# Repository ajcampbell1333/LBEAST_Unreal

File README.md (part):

# LBEAST SDK for Unreal Engine

**Location-Based Entertainment Activation Standard Toolkit (LBEAST)** - A comprehensive SDK for developing VR/AR Location-Based Entertainment experiences in UE5 with support for AI facial animation, large hydraulic haptics, and embedded systems integration.

<details>
<summary><strong>⚠️Author Disclaimer:</strong></summary>

<blockquote>
This is a brand new plugin as of November 2025. Parts of it are not fully fleshed out. The author built LBE activations for Fortune 10 brands over the past decade. This is the dream toolchain he wishes we had back then, but it probably still contains unforeseen bugs in its current form. V1.0 is considered Alpha, and Alpha is not show-ready. Beta (2.0) will be the first version we attempt to use in professional venues. If you're seeing this message, it's because LBEAST has yet to deploy on a single professional project. Please use this code at your own risk. Also, this plugin provides code that may or may not run on systems your local and state officials may classify as  "amusement rides" or "theme park rides" which may fall under ASTM standards or other local regulations. LBEAST's author disclaims any and all liability for any use of this code, including for safety of guests or patrons, regulatory readiness, etc. Please review the local regulations in your area prior to executing this code in any public venue. You are responsible for compliance in your state.
</blockquote>

</details><br>

---

## 📖 Overview

LBEAST is a comprehensive SDK for developing VR and AR Location-Based Entertainment (LBE) experiences. This repository contains the **Unreal Engine 5.5.4** implementation of the LBEAST SDK.

The LBEAST SDK democratizes LBE development by providing:
- **Experience Genre Templates** - Drag-and-drop complete LBE solutions
- **Low-Level APIs** - Technical modules for custom integration between game engine and various physical systems
- **AI-Driven Facial Animation** for immersive theater live actors (automated w/ NVIDIA ACE)
- **Wireless Trigger Controls** - Embedded buttons in costume/clothing for narrative state machine control through WiFi/Bluetooth
- **Large-Scale Hydraulic Haptics** for lift/motion platforms
- **Embedded Systems Integration** for costume-/prop-/wall-/furniture-mounted interfaces
- **Embedded Sensors** temperature, motion, face, and body tracking sensors to trigger escape room actions
- **Co-located XR Multiplayer LAN Experiences** with Unreal Replication + GAS
- **HMD and Hand Tracking** via OpenXR (Unreal's native XR system)
- **6DOF Tracking** with SteamVR trackers and future extensibility

<details>
<summary><strong>⚠️OpenXR Note:</strong></summary>

<blockquote>
LBEAST uses **OpenXR exclusively** for all HMD and hand tracking access through Unreal Engine's native XR system (`IXRTrackingSystem`, `IHandTracker`). If OpenXR is not desired for your LBE deployment for any reason, but you still want to use an LBEAST experience genre template to get started, there may be some customization necessary in `LBEASTHandGestureRecognizer` and in some of the Experience classes. Anywhere OpenXR is referenced, you may need to create an alternative version of that class with your SDK of choice replacing OpenXR usage.

</blockquote> 

</details>   
<br>

> **🔗 Unity Version:** Also available at [github.com/scifiuiguy/lbeast_unity](https://github.com/scifiuiguy/lbeast_unity)

## 📚 Table of Contents

<details>
<summary><strong>THIS README</strong></summary>

<blockquote>

- [Overview](#overview)
- [Philosophy](#philosophy)
- [Three-Tier Architecture](#three-tier-architecture)
- [Standard Pop-up Layout](#standard-pop-up-layout)
- [Features](#features)
- [Installation](#-installation)
- [Quick Start](#quick-start)
- [Architecture](#architecture)
- [Module Structure](#module-structure)
- [Networking](#networking)
- [Hardware Integration](#hardware-integration)
- [Use Cases](#use-cases)
- [Dedicated Server & Server Manager](#dedicated-server--server-manager)
- [Network Configuration](#network-configuration)
- [Embedded System Philosophy](#embedded-system-philosophy)
- [Embedded System Nuts & Bolts](#-embedded-system-nuts--bolts)
- [Roadmap](#-roadmap)
- [Support](#support)
- [License](#license)
- [Contributing](#contributing)
- [Credits](#credits)

</blockquote>

</details>

<details>
<summary><strong>OTHER READMEs IN THIS PROJECT</strong></summary>

<blockquote>

**Low-Level APIs:**
- [LBEASTAI API README](https://github.com/scifiuiguy/lbeast_unreal/blob/main/Source/LBEASTAI/README.md) - `Source/LBEASTAI/README.md`
- [VRPlayerTransport README](https://github.com/scifiuiguy/lbeast_unreal/blob/main/Source/LBEASTCore/Public/VRPlayerTransport/README.md) - `Source/LBEASTCore/Public/VRPlayerTransport/README.md`
- [Input README](https://github.com/scifiuiguy/lbeast_unreal/blob/main/Source/LBEASTCore/Public/Input/README.md) - `Source/LBEASTCore/Public/Input/README.md`
- [VOIP README](https://github.com/scifiuiguy/lbeast_unreal/blob/main/Source/VOIP/README.md) - `Source/VOIP/README.md`
- [EmbeddedSystems README](https://github.com/scifiuiguy/lbeast_unreal/blob/main/Source/EmbeddedSystems/README.md) - `Source/EmbeddedSystems/README.md`
- [ProLighting README](https://github.com/scifiuiguy/lbeast_unreal/blob/main/Source/ProLighting/README.md) - `Source/ProLighting/README.md`

**Experience Genre Templates:**
- [AIFacemask Experience README](https://github.com/scifiuiguy/lbeast_unreal/blob/main/Source/LBEASTExperiences/Private/AIFacemask/README.md) - `Source/LBEASTExperiences/Private/AIFacemask/README.md`

**Firmware Examples:**
- [FirmwareExamples README](https://github.com/scifiuiguy/lbeast_unreal/blob/main/FirmwareExamples/README.md) - `FirmwareExamples/README.md`
- [GunshipExperience README](https://github.com/scifiuiguy/lbeast_unreal/blob/main/FirmwareExamples/GunshipExperience/README.md) - `FirmwareExamples/GunshipExperience/README.md`
- [FlightSimExperience README](https://github.com/scifiuiguy/lbeast_unreal/blob/main/FirmwareExamples/FlightSimExperience/README.md) - `FirmwareExamples/FlightSimExperience/README.md`
- [SuperheroFlightExperience README](https://github.com/scifiuiguy/lbeast_unreal/blob/main/FirmwareExamples/SuperheroFlightExperience/README.md) - `FirmwareExamples/SuperheroFlightExperience/README.md`
- [EscapeRoom README](https://github.com/scifiuiguy/lbeast_unreal/blob/main/FirmwareExamples/EscapeRoom/README.md) - `FirmwareExamples/EscapeRoom/README.md`
- [Base Examples README](https://github.com/scifiuiguy/lbeast_unreal/blob/main/FirmwareExamples/Base/Examples/README.md) - `FirmwareExamples/Base/Examples/README.md`
- [Base Templates README](https://github.com/scifiuiguy/lbeast_unreal/blob/main/FirmwareExamples/Base/Templates/README.md) - `FirmwareExamples/Base/Templates/README.md`

**Examples & Utilities:**
- [ServerManager README](https://github.com/scifiuiguy/lbeast_unreal/blob/main/Source/Examples/ServerManager/README.md) - `Source/Examples/ServerManager/README.md`

</blockquote>

</details>

---

## 💭 Philosophy

<details>
<summary><strong>Why LBEAST?</strong></summary>

<blockquote>

Home console VR usage is nascent and difficult despite being steadily on the rise:
* 80 million monthly active users in the U.S. in 2025
* up 60% from 2020
* 10% of Americans started using VR regularly so far this decade

If that growth holds, we might reach 100 million regular VR users by end-of-decade, more than 1/4 of the population. It's not smartphone-era growth, but it's steady.

BUT...

Content budgets are skin-and-bone. 

Building for VR requires specialty talent compared to film/TV/gaming, and every dollar spent goes half as far due to...
* deeper fidelity challenges
* bigger QA hurdles
* evil perf op constraints

VR devs need a leg up. The industry has been in a funding desert since the Pandemic. "VR is all hype" rumors put the dev community on a respirator, and we never got off the ropes.

I get where investors are coming from. We're 10 years into modern VR. They need proof of ROI. We need to deliver in the black. We need better tools. We were building cars without factories.

**A good analogy for 21st century VR Distro - Movie Theaters:**
If a Hollywood studio invested millions on a new film in the 80s, they'd be sunk if there were no 35mm projector and no movie theaters hungry to roll the next hit.

**An even better analogy - the JAMMA Arcade Spec:**
In 1985, the arcade industry was in a slump. All the arcade boxes were proprietary. Venues had to buy a new arcade box for every game. Devs had to design a whole arcade box for just THEIR game. Enter the JAMMA Spec. Suddenly venues could leave the same box in place and swap a card, and it's a new game! Same hardware, fresh regular content. Devs could focus on the game knowing reliable hardware was already on-site.

We need that for the VR industry:
* Devs need to be able to focus on dev, not hardware
* Venues need standard hardware so devs can bring them regular new content.

We have an chicken-egg situation. A standard spec for VR LBE is what we need.

Enter LBEAST. Free, open-source, plug-n-play across multiple genres.

</blockquote>

</details>

<details>
<summary><strong>Who is LBEAST for?</strong></summary>

<blockquote>

LBEAST is for VR venues, trade show designers, and professional dev teams designing  permanent, semi-permanent, or pop-up Location-Based Entertainment installations. LBEAST is a professional-grade toolchain designed for teams of programmers and technical artists.

**Target audiences:**
- **Theme park attraction designers/engineers/production staff** - Building immersive attractions with motion platforms, embedded systems, and live actor integration
- **VR Arcade venue designers/engineers/production staff** - Deploying multiplayer VR experiences with synchronized motion and professional audio/lighting
- **Brands at trade shows** interested in wowing audiences with VR
- **3rd-party VR developers** who want to deploy new content rapidly to theme parks and VR Arcades
- **VR educators** who want to expose students to professional toolchains used in commercial LBE production

The SDK provides:
- ✅ **C++ programmers** with robust APIs and extensible architecture
- ✅ **Blueprint artists** with drag-and-drop components and visual scripting
- ✅ **Content teams** with rapid deployment capabilities
- ✅ **Commercial projects** with free-to-use, MIT-licensed code

</blockquote>

</details>

<details>
<summary><strong>Who is LBEAST not for?</strong></summary>

<blockquote>

Developers with little or no experience with C++ may struggle to put LBEAST to its fullest use. It is meant for a scale of production that would be challenging for lone developers. However, it can be a great learning tool for educators to prepare students to work on professional team projects.

**Important notes:**
- LBEAST is **not** a no-code solution. It requires programming knowledge (C++ or Blueprint scripting) to customize experiences beyond the provided templates.
- LBEAST is designed for **team-based production** with multiple developers, technical artists, and production staff.
- LBEAST provides blueprints, but it assumes tech art team members have access to C++ programmers on the team to back them up for customization.

</blockquote>

</details>

---

## 🏗️ Three-Tier Architecture

LBEAST uses a modular three-tier architecture for code organization and server/client deployment.

### Code and Class Structure

<details>
<summary><strong>Tier 1: Low-Level APIs (Technical Modules)</strong></summary>

<blockquote>

Foundation modules providing core functionality:
- `LBEASTCore` - HMD/tracking abstraction, networking
- `LBEASTAI` - Low-level AI API (LLM, ASR, TTS, container management)
- `LargeHaptics` - Platform/gyroscope control
- `EmbeddedSystems` - Microcontroller integration
- `ProAudio` - Professional audio console control via OSC
- `ProLighting` - DMX lighting control (Art-Net, USB DMX)
- `Retail` - Cashless tap card payment interface for VR tap-to-play
- `VOIP` - Low-latency voice communication with 3D HRTF spatialization
- `RF433MHz` - 433MHz RF trigger/receiver API for wireless button/remote control (rolling code support, USB receiver abstraction)

**Use these when:** Building custom experiences from scratch with full control.

</blockquote>

</details>

<details>
<summary><strong>Tier 2: Experience Genre Templates (Pre-Configured Actors)</strong></summary>

<blockquote>

Ready-to-use complete experiences combining multiple APIs:
- `AAIFacemaskExperience` - Live actor-driven multiplayer VR with wireless trigger buttons controlling automated AI facemask performances
- `AMovingPlatformExperience` - A 4-gang hydraulic platform on which a single VR player stands while hooked to a suspended cable harness to prevent falling
- `AGunshipExperience` - 4-player seated platform with 4DOF hydraulic motion driven by a 4-gang actuator platform with a player strapped in at each corner, all fixed to a hydraulic lift that can dangle players a few feet in the air
- `ACarSimExperience` - A racing/driving simulator where 1-4 player seats are bolted on top of a 4-gang hydraulic platform
- `AFlightSimExperience` - A single player flight sim with HOTAS controls in a 2-axis gyroscopic cockpit built with servo motors for pitch and roll.
  - **⚠️ Requires outside-in tracking with cockpit-mounted trackers for Space Reset feature (see FlightSimExperience/README.md)** 
- `AEscapeRoomExperience` - Puzzle-based escape room with embedded door lock/prop latch solenoids, sensors, and pro AV integration for light/sound and live improv actors
- `AGoKartExperience` - Electric go-karts, bumper cars, race boats, or bumper boats augmented by passthrough VR or AR headsets enabling overlaid virtual weapons and pickups that affect the performance of the vehicles
- `ASuperheroFlightExperience` - A dual-hoist-harness-and-truss system that lifts a player into the air and turns them prone to create the feeling of superhero flight as they punch fists out forward, up, or down

**Use these when:** Rapid deployment of standard LBE genres.

</blockquote>

</details>

<details>
<summary><strong>Tier 3: Your Custom Game Logic</strong></summary>

<blockquote>

Build your specific experience (Tier 3) on top of templates (Tier 2) or APIs (Tier 1).

</blockquote>

</details>

<details>
<summary><strong>When to Use What?</strong></summary>

<blockquote>

| Scenario | Use This | Why |
|----------|----------|-----|
| Building a gunship VR arcade game | `AGunshipExperience` | Pre-configured for 4 players, all hardware setup included |
| Building a racing game | `ACarSimExperience` | Simplified driving API, optimized motion profiles |
| Building a space combat game | `AFlightSimExperience` | HOTAS integration ready, continuous rotation supported |
| Custom 3-player standing platform | Low-Level APIs | Need custom configuration not covered by templates |
| Live actor-driven escape room | `AAIFacemaskExperience` | Wireless trigger buttons in costume control narrative state machine, automated AI facemask performances |
| Puzzle-based escape room | `AEscapeRoomExperience` | Narrative state machine, door locks, prop sensors, embedded systems |
| Go-kart racing with VR/AR overlay | `AGoKartExperience` | Passthrough VR/AR support, virtual weapons, item pickups, projectile combat |
| Superhero flight simulation | `ASuperheroFlightExperience` | Dual-winch suspended harness, gesture-based control, free-body flight |
| Unique hardware configuration | Low-Level APIs | Full control over all actuators and systems |

**Rule of thumb:** Start with templates, drop to APIs only when you need customization beyond what templates offer.

</blockquote>

</details>

### LAN Server/Client Configuration

<details>
<summary><strong>Local Command Console</strong></summary>

<blockquote>

```
┌─────────────────────────────────────────────────┐
│  Single PC (Command Console + Server Manager)   │
│  ─────────────────────────────────────────────  │
│  • Command Console UI (UMG Panel)               │
│  • Server Manager (Dedicated Server Backend)    │
│  • All processing on one machine                │
└──────────────────────┬──────────────────────────┘
                       │
                       │ UDP WiFi (LAN)
                       │
        ┌──────────────┴──────────────┐
        │                             │
        ▼                             ▼
   ┌─────────┐                  ┌─────────┐
   │ VR HMD  │                  │ VR HMD  │
   │(Player) │                  │(Live    │
   │   1     │                  │ Actor 1)│
   └─────────┘                  └─────────┘
        │                             │
        │                             │
   ┌────┴────┐                  ┌────┴────┐
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
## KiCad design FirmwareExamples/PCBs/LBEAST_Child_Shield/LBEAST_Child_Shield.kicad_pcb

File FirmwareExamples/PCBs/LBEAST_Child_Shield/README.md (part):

# LBEAST Child Shield

**Also known as:** LBCS

## Overview

The Child Shield is a simplified derivative of the Universal Shield (LBUS). It keeps the same ESP32-S3 parent ECU pin map and Ethernet PHY but reduces the aux bus to **one** RJ45 port and drops CAN entirely. The goal is to provide a tiny, inexpensive parent/child hybrid board for installations that only need a single downstream device or a dedicated “mini LBUS” inside a prop or remote enclosure.

**Current design goals:**
- 1× RJ45 (Ethernet only). No CAN, no extra ADC/PWM breakouts.
- Powered either from the parent LBUS via the PoE/DIP/diode rail **or** from a local USB‑C Li‑ion pack (5 V input only).
- No onboard buck converter, reverse-polarity MOSFET, or fan header—the board expects regulated 5 V and relies on passive cooling.
- Keep the ESP32-S3 personality-adapter footprint for firmware parity with LBUS.
- Target the smallest possible PCB outline for costume props, handheld gadgets, and wireless sensor clusters.

> Until this document is fleshed out, refer to the [Universal Shield README](../LBEAST_Universal_Shield/README.md) for fully documented schematics, BOM, and power notes. The Child Shield uses that design as its baseline.

---

## Documentation Template (to be completed)

The sections below intentionally keep the same structure as the Universal Shield README. Each section contains a short note describing what still needs to be written for the Child Shield variant.

<details>
<summary><strong>Electronic Control Unit (ECU)</strong></summary>

<div style="margin-left: 20px;">
Provide a summarized ECU primer tailored to the Child Shield. Emphasize that this board is meant for ultra-lightweight, Ethernet-only nodes (wearables, handheld props, remote sensors) that either sip power from LBUS or carry their own USB‑C battery.
</div>

</details>

<details>
<summary><strong>Child Shield Role in the LBUS Ecosystem</strong></summary>

<div style="margin-left: 20px;">
Explain how the Child Shield can operate as:
- A “micro parent” when only one Ethernet child device is required.
- A pre-wired breakout that ships with finished props or costume pieces (power via USB‑C).
- A remote Ethernet-only repeater that backhauls data to a full LBUS when PoE is toggled on.
Document the rules for when to toggle PoE off (battery-powered mode) vs on (LBUS-powered mode), and reiterate that no CAN bus is present on this variant.
</div>

</details>

<details>
<summary><strong>Motivation / Modularity Advantage</strong></summary>

<div style="margin-left: 20px;">
Describe the cost/space savings of a single-port shield vs. an 8-port backplane. Document the target BOM (<$15 at scale) and the intended use cases (wearables, props, distributed IoT nodes).
</div>

</details>

<details>
<summary><strong>Key Features (Child Shield)</strong></summary>

<div style="margin-left: 20px;">
- 1× RJ45 aux port (Ethernet only; same pin map as AUX1 on LBUS)
- ESP32-S3 socket (same as Universal Shield) for firmware compatibility
- Power flexibility: accepts 5 V from LBUS PoE rail or from local USB‑C input
- No CAN transceiver, no LM2576 buck converter, no fan header
- Reduced board outline sized for small enclosures (exact dimensions TBD)
</div>

</details>

<details>
<summary><strong>High-Level Block Diagram</strong></summary>

<div style="margin-left: 20px;">
Add a simplified ASCII diagram once schematic capture begins. Use the Universal Shield diagram as a starting point, but replace the 8-port block with a single “Aux Port J1” call-out.
</div>

</details>

<details>
<summary><strong>Project Files</strong></summary>

<div style="margin-left: 20px;">
Planned filenames (to be created when schematic/PCB are captured):
- `LBEAST_Child_Shield.kicad_pro`
- `LBEAST_Child_Shield.kicad_sch`
- `LBEAST_Child_Shield.kicad_pcb`
- `LBEAST_Child_Shield.kicad_prl`
Note: Until those exist, the folder contains a working copy of the Universal Shield project as a springboard.
</div>

</details>

<details>
<summary><strong>Power Architecture</strong></summary>

<div style="margin-left: 20px;">
Document the simplified power path:
- 5 V PoE from LBUS → DIP switch → diode → RJ45 pin 4
- Optional USB‑C 5 V input (with reverse-current blocking so it doesn’t backfeed LBUS)
- ESP32-S3 VIN receives 5 V directly (no onboard buck). Note USB‑C current limit assumptions.
Clarify fuse strategy (likely deferred to parent LBUS) and diode usage.
</div>

</details>

<details>
<summary><strong>Component Set / BOM</strong></summary>

<div style="margin-left: 20px;">
Create a slimmed-down BOM once the schematic is finalized. Expected parts:
- ESP32-S3 headers + UART debug header
- LAN8720A PHY + 25 MHz crystal + magnetics
- Single RJ45 (MTJ-883X1 or similar)
- USB‑C connector (5 V only, no PD)
- DIP switch + Schottky diode for PoE gating
- Bypass caps, status LEDs, optional ESD protection
</div>

</details>

<details>
<summary><strong>Aux Port Pinout (Single-Port)</strong></summary>

<div style="margin-left: 20px;">
Reuse the T568B table from the Universal Shield but annotate that only J1 exists. Clarify how ADC/PWM mapping changes (likely reusing AUX1 nets).
</div>

</details>

<details>
<summary><strong>Enclosure / Mechanical Notes</strong></summary>

<div style="margin-left: 20px;">
- Planned enclosure: **Polycase TerraForm TF-1741TX** (ABS, tool-less lid) – [Product page](https://www.polycase.com/tf-1741tx). Fits a single RJ45, USB-C, and low-profile ESP32 module. Document mounting-hole pattern once the PCB outline is finalized.
- Add measurements for the smaller board, recommended potting volumes, and any mounting-hole changes once the layout exists. Capture whether standoffs align with the TF-1741TX bosses or require adhesive-backed posts.
</div>

</details>

<details>
<summary><strong>Future Work</strong></summary>

<div style="margin-left: 20px;">
- Finalize schematic/layout
- Generate dedicated 3D models and assembly drawings
- Produce a minimal BOM + fabrication notes
- Write firmware notes for "single-port parent" mode
- **TP4056 Battery Integration** - Integrate TP4056 USB-C lithium battery charging module directly onto the Child Shield PCB with exposed battery connection pads (B+/B-). Enables portable, battery-powered operation for wearable props, handheld gadgets, and remote sensor clusters. Includes power path management (USB-C charging + battery power), boost converter for 5V output (ESP32 dev board compatibility), and battery protection circuitry. See v2.0 roadmap for implementation details.
</div>

</details>

<details>
<summary><strong>High-Level Component Diagram</strong></summary>

<div style="margin-left: 20px;">

```
          ┌────────────────────────────────────────┐
          |                                        │
    ┌─────▲───────┐    ┌───────┐ +5V               │
    │ Barrel Jack │───→│LM2576 │────┐       ┌──────▼───────┐
    │  12V/24V    │    │ Buck  │    │       │ 12/24V Fan   │
    └─────────────┘    └───────┘    │       └───────┬──────┘
                           │+5V     │               ▼
                           │        │  ┌────────────────────────┐
                           │        └─→│         ESP32-S3       │
                           │           │      (Motherboard)     │
                           │           └──▲──────────────▲──────┘
                           │              │              │
                           │         ┌────▼────┐    ┌────▼────┐
                           │         │LAN8720A │    │ADM3057E │
                           │         │Ethernet │    │ CAN-FD  │
                           │         └────▲────┘    └────▲────┘
                           │              │              │
                           │              │         ┌────▼─────┐
                           │              │         │CAN 3-pin │
                           │              │         └──────────┘         
                    ┌──────▼──────────────▼──────────────────┐   
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
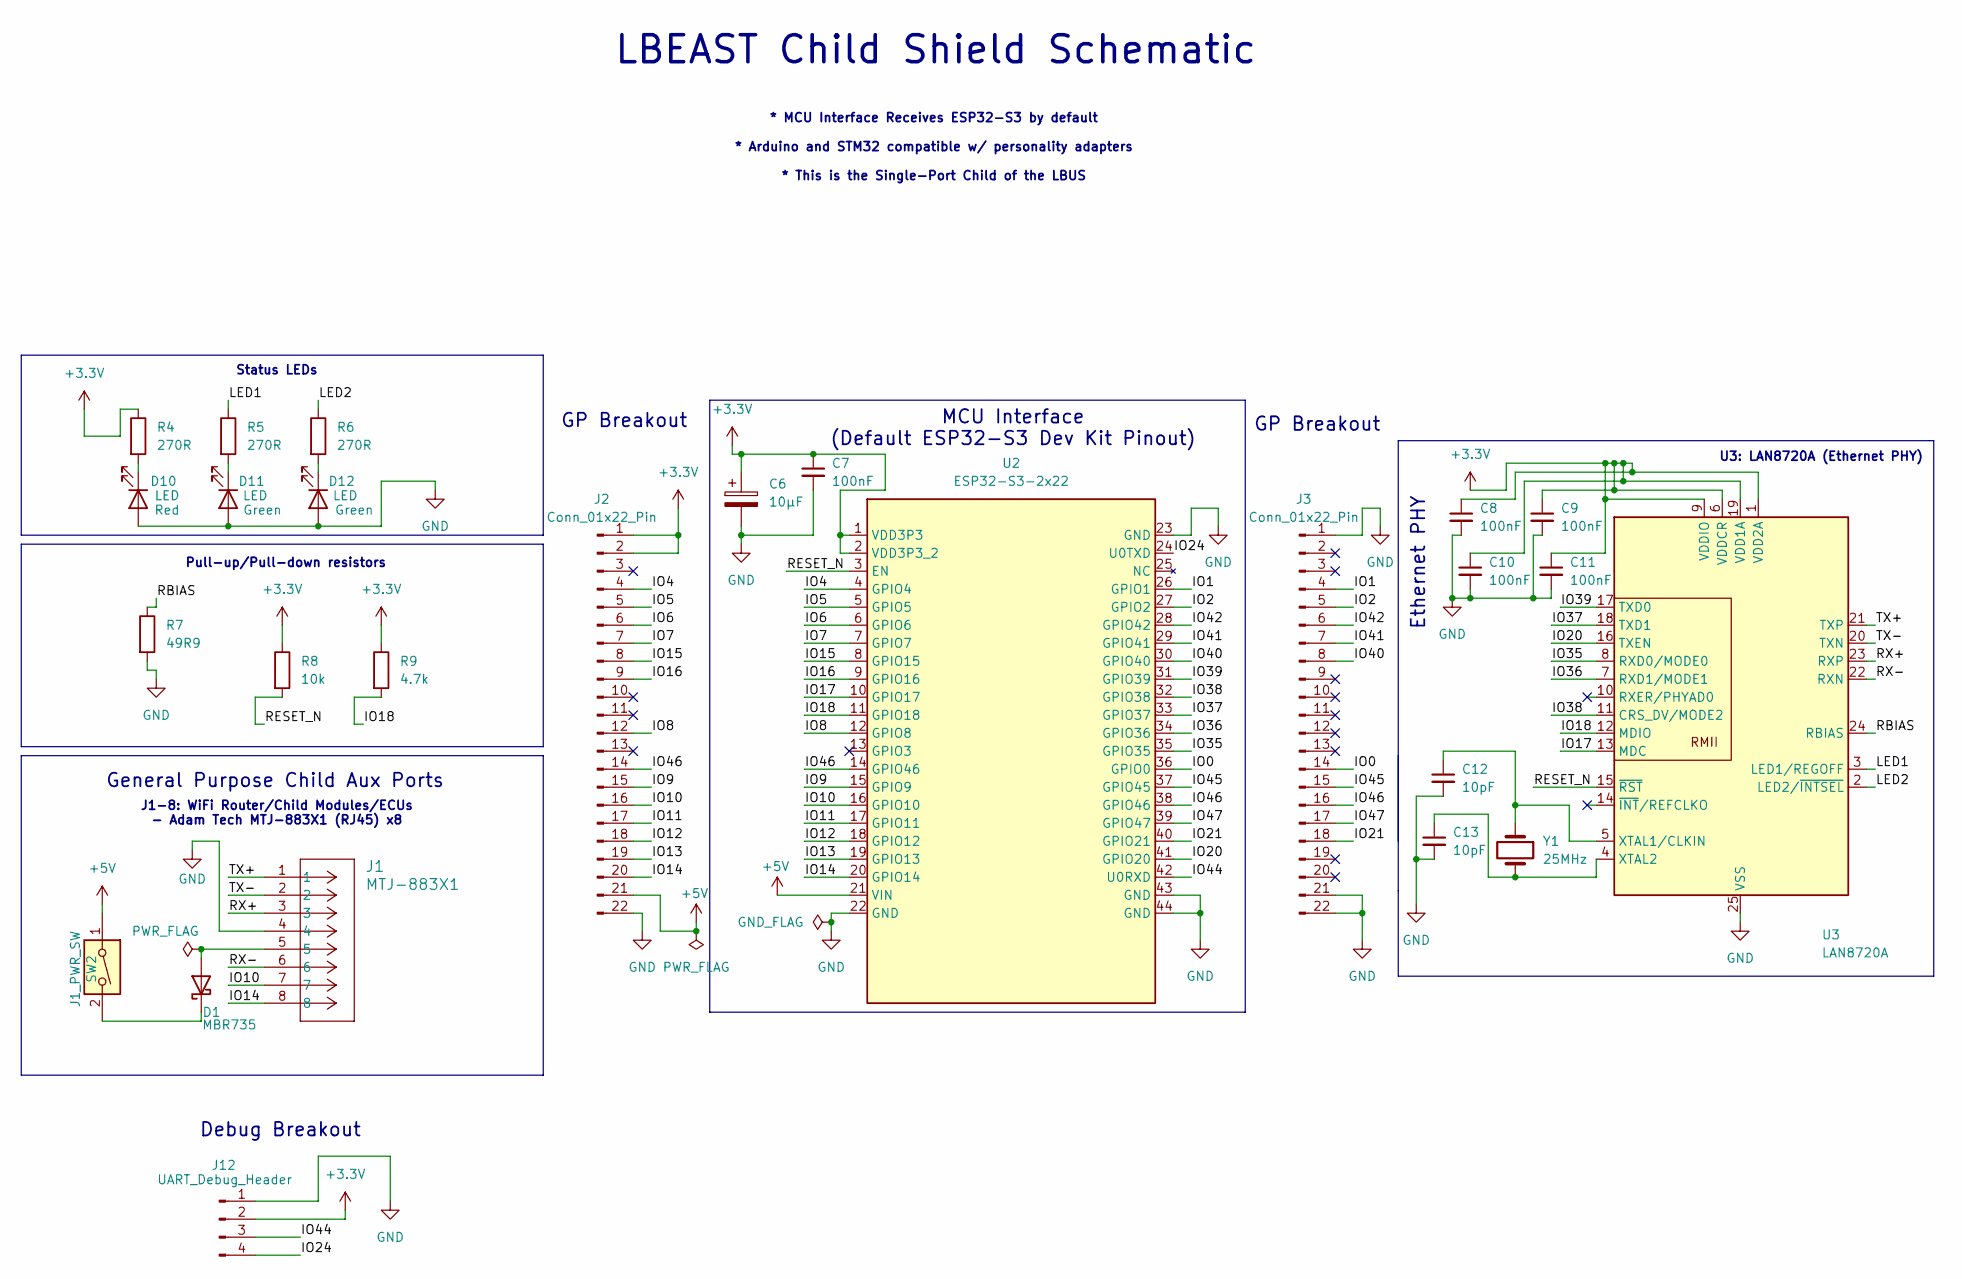
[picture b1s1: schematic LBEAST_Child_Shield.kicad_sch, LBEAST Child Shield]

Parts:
C6: 10µF; CP_EIA-3216-18_Kemet-A
C7, C8, C9, C10, C11: 100nF; C_0805_2012Metric
C12, C13: 10pF; C_0805_2012Metric
D1: MBR735; TO-220-2_Vertical
D10, D11, D12: LED; LED_0805_2012Metric
J1: MTJ-883X1; CONN_MTJ-883X1_ADM
J2, J3: Conn_01x22_Pin; PinHeader_1x22_P2.54mm_Vertical
J12: UART_Debug_Header; PinHeader_1x04_P2.54mm_Vertical
R4, R5, R6: 270R; R_0805_2012Metric
R7: 49R9; R_0805_2012Metric
R8: 10k; R_0805_2012Metric
R9: 4.7k; R_0805_2012Metric
SW2: J1_PWR_SW; SW_DIP_SPSTx01_Slide_6.7x4.1mm_W6.73mm_P2.54mm_LowProfile_J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
U2: ESP32-S3-2x22; ESP32-S3_2x22_Header_v3
U3: LAN8720A; VQFN-24-1EP_4x4mm_P0.5mm_EP2.5x2.5mm_ThermalVias
Y1: 25MHz; Crystal_SMD_3225-4Pin_3.2x2.5mm

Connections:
+3.3V: C6.1, C7.1, C8.1, C9.1, C10.1, C11.1, J2.1, J2.2, J12.2, R4.1, R8.1, R9.1, U2.1 (VDD3P3), U2.2 (VDD3P3_2), U3.1 (VDD2A), U3.6 (VDDCR), U3.9 (VDDIO), U3.19 (VDD1A)
+5V: J2.21, SW2.1, U2.21 (VIN)
/IO0: J3.14, U2.36 (GPIO0)
/IO1: J3.4, U2.26 (GPIO1)
/IO2: J3.5, U2.27 (GPIO2)
/IO4: J2.4, U2.4 (GPIO4)
/IO5: J2.5, U2.5 (GPIO5)
/IO6: J2.6, U2.6 (GPIO6)
/IO7: J2.7, U2.7 (GPIO7)
/IO8: J2.12, U2.12 (GPIO8)
/IO9: J2.15, U2.15 (GPIO9)
/IO10: J1.7, J2.16, U2.16 (GPIO10)
/IO11: J2.17, U2.17 (GPIO11)
/IO12: J2.18, U2.18 (GPIO12)
/IO13: J2.19, U2.19 (GPIO13)
/IO14: J1.8, J2.20, U2.20 (GPIO14)
/IO15: J2.8, U2.8 (GPIO15)
/IO16: J2.9, U2.9 (GPIO16)
/IO17: U2.10 (GPIO17), U3.13 (MDC)
/IO18: R9.2, U2.11 (GPIO18), U3.12 (MDIO)
/IO20: U2.41 (GPIO20), U3.16 (TXEN)
/IO21: J3.18, U2.40 (GPIO21)
/IO24: J12.4, U2.24 (U0TXD)
/IO35: U2.35 (GPIO35), U3.8 (RXD0/MODE0)
/IO36: U2.34 (GPIO36), U3.7 (RXD1/MODE1)
/IO37: U2.33 (GPIO37), U3.18 (TXD1)
/IO38: U2.32 (GPIO38), U3.11 (CRS_DV/MODE2)
/IO39: U2.31 (GPIO39), U3.17 (TXD0)
/IO40: J3.8, U2.30 (GPIO40)
/IO41: J3.7, U2.29 (GPIO41)
/IO42: J3.6, U2.28 (GPIO42)
/IO44: J12.3, U2.42 (U0RXD)
/IO45: J3.15, U2.37 (GPIO45)
/IO46: J2.14, J3.16, U2.14 (GPIO46), U2.38 (GPIO46)
/IO47: J3.17, U2.39 (GPIO47)
/LED1: R5.1, U3.3 (LED1/REGOFF)
/LED2: R6.1, U3.2 (LED2/~INTSEL)
/RBIAS: R7.1, U3.24 (RBIAS)
/RESET_N: R8.2, U2.3 (EN), U3.15 (~RST)
/RX+: J1.3, U3.23 (RXP)
/RX-: J1.6, U3.22 (RXN)
/TX+: J1.1, U3.21 (TXP)
/TX-: J1.2, U3.20 (TXN)
GND: C6.2, C7.2, C8.2, C9.2, C10.2, C11.2, C12.2, C13.2, D10.2 (A), D11.2 (A), D12.2 (A), J1.4, J2.22, J3.1, J3.21, J3.22, J12.1, R7.2, U2.22 (GND), U2.23 (GND), U2.43 (GND), U2.44 (GND), U3.25 (VSS), Y1.3
unnamed: D1.2 (A), J1.5
unnamed: D1.1 (K), SW2.2
unnamed: D10.1 (K), R4.2
unnamed: D11.1 (K), R5.2
unnamed: D12.1 (K), R6.2
unnamed: C12.1, U3.5 (XTAL1/CLKIN), Y1.1
unnamed: C13.1, U3.4 (XTAL2), Y1.2

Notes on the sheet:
GP Breakout
J1-8: WiFi Router/Child Modules/ECUs - Adam Tech MTJ-883X1 (RJ45) x8
General Purpose Child Aux Ports
Debug Breakout
Ethernet PHY
Pull-up/Pull-down resistors
U3: LAN8720A (Ethernet PHY)
* MCU Interface Receives ESP32-S3 by default * Arduino and STM32 compatible w/ personality adapters * This is the Single-Port Child of the LBUS
LBEAST Child Shield Schematic
Status LEDs
MCU Interface (Default ESP32-S3 Dev Kit Pinout)

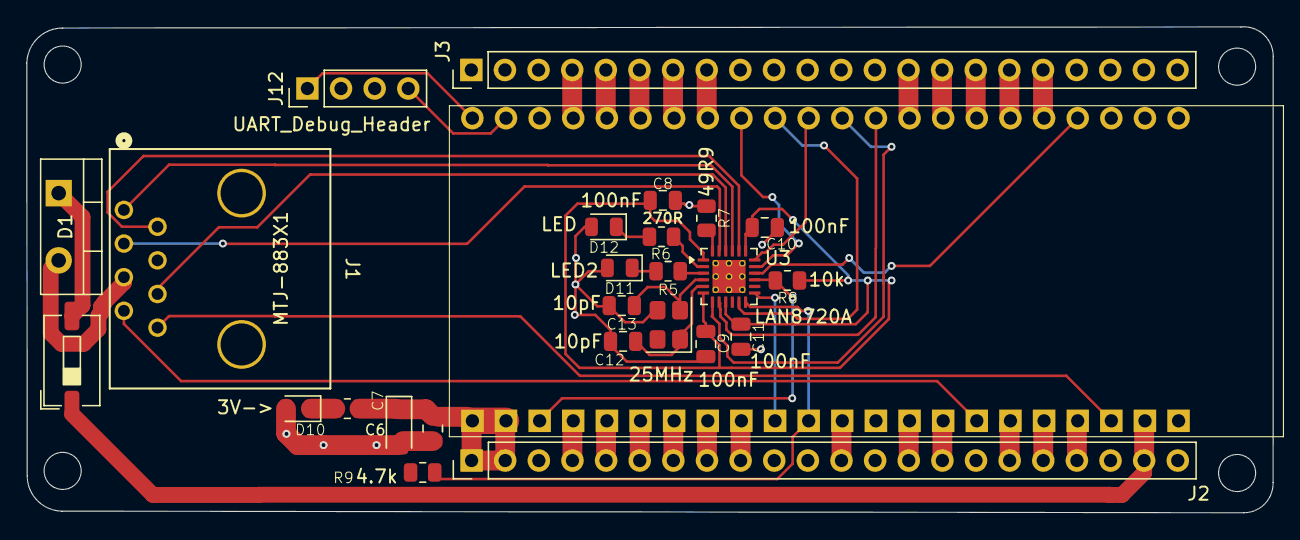
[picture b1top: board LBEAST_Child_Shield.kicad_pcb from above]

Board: 2 copper layers, 94.1 x 36.7 mm, 26 parts (0 on the bottom side), 51 nets.

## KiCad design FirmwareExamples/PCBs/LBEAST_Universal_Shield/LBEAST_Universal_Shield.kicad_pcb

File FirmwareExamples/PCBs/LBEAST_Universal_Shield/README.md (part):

# LBEAST Universal Shield

**Also known as:** LBUS, Uni-Shield

## Overview

**Plug-n-Play Embedded Systems - an Absolute Necessity for Next-Level LBE:**

The LBEAST Universal Shield ("LBUS" or "Uni-Shield") is a multi-platform ECU that provides unified connectivity and control for all LBEAST firmware applications. But what is it for? What does it do? ECU? What the heck is even that?

<details>
<summary><strong>Electronic Control Unit (ECU)</strong></summary>

<div style="margin-left: 20px;">

It's sort of like the little computer hidden behind the dashboard in your car. It's not a supercomputer... quite the opposite. It costs a few dollars to buy a few dev boards on Amazon and deploy them as ECUs by flashing programs onto them. If you've done IoT with Arduino, ESP32, or STM32... congrats! You're an ECU programmer!

ECUs are nowhere near as powerful or expensive as a smartphone, but they can be MUCH smaller and lighter, so they're great for speciatly tasks hidden in tight spaces. Custom-built processors with dedicated task lists... hardware AND firmware are built to do that task list and nothing more. You don't run a program from a list of programs. The whole ECU's operating system IS the program. It's a one-program device. That's why we say "firmware." To update or replace the latest build, you flash A.K.A. replace all the code running on the device.

</div>

</details>

<details>
<summary><strong>LBUS is an ECU Network</strong></summary>

<div style="margin-left: 20px;">

LBUS is the ECU you should start with for LBEAST-ready installations, and it can netowrk with copies of itself or any other custom ECU that communicates over ethernet, bluetooth, 433MHz RF, and/oror Wifi. It's powered by your choice of ESP32, Arduino, or STM32. LBUS serves as Union Station for all the data in any system you build from scratch. It enables you to deploy hydraulics, haptics, big servo motors that can spin customers upside down, etc. It let's you hide Child ECUs inside the chassis of a ride, in the clothing of immersive actors, in props, and/or in the decorated walls of an AR experience.

</div>

</details>

<details>
<summary><strong>Doesn't the LBE Industry already do things like this?</strong></summary>

<div style="margin-left: 20px;">

Most VR and AR experiences are driven by local multiplayer servers built via game engines so that co-located players can see a shared experience while an employee monitors the state of the game loop. Occasionally, these LBE events have advanced integration with a variety of other systems, including lights, pro audio, communication with smartphones and tablets for extra control.

However, it is rare to see a VR experience that includes theme-park attraction technology like large hydraulic actuators or embedded ECUs in costumes worn by immersive actors, in props, and in scenery. This is because the full palette of immersive technologies is complex and expensive. VR budgets in the 2020s generally prohibit us from "next-level"-ing VR experiences in most cases. It's not that we can't integrate the tech. It has just been TOO EXPENSIVE.

</div>

</details>

<details>
<summary><strong>The LBUS Fixes That!</strong></summary>

<div style="margin-left: 20px;">

LBUS is open-source. It's near free! And it's already fully built and running, ready for you to take and use and skin it with new assets and stand up a new LBE event in a fraction of the time!

LBUS fully integrated with both major game engines (Unity/Unreal) in a ready-to-play local multiplayer server project that has a bunch of LBE templates ready-to-play. A single out-of-the-box LBUS has a bill-of-materials of less than $200 to build 5 copies. LBEAST is not a company. The PCB files are in the git repo, ready for you to send to any PCB manufacturer to order boards at a tiny fraction of the cost of using PLCs. A single LBUS unit supports 8 simultaneous child ECUs via Ethernet while providing galvanically isolated CAN-FD connectivity for high-current device control.

</div>

</details>

<details>
<summary><strong>Just like JAMMA Resurrected the Arcade Industry in 1985</strong></summary>

<div style="margin-left: 20px;">

The whole industry was proprietary and in a big recession. Developers and venues needed a leg up. Arcade retailers were struggling with the cost of buying anew arcade box every time a new game came out.

Suddenly, the JAMMA spec let them pop a new game card into the same box they already had. Games started launching 10X as fast as before. New content every day! Developers didn't have to worry about box manufacture anymore. They could just focus on the game.

VR is VERY proprietary today. What if you want to build a hydraulic sim and make it feel like a theme park ride? Where do you even begin? You have to hire mechanical engineers and software engineers, and they'll build a complex sytem that works ONLY at your venue. Good luck getting 10 VR development teams to build something for that.

The industry needs standard specs. If you already built a hydraulic rig to a known spec, and EVERY VR dev team knows that spec already, they can ALL starting building experiences for it. It's a chicken/egg challenge, and neither can happen first until we have a spec. That's why LBUS is critical for VR2.0.

</div>

</details>

<details>
<summary><strong>Modularity Advantage</strong></summary>

<div style="margin-left: 20px;">

Unlike traditional PLCs (Programmable Logic Controllers) that require proprietary hardware and software ecosystems, the Universal Shield embraces modularity through open-source microcontrollers. This approach offers several key advantages: **cost efficiency** (microcontrollers are significantly less expensive than PLCs), **flexibility** (choose the MCU platform that best fits your application), **rapid development** (standard development tools and languages), **scalability** (easily expand with additional child ECUs), and **future-proofing** (upgrade individual components without replacing entire systems). The Universal Shield's personality adapter system allows the same hardware to support multiple MCU platforms, while the 8-port Ethernet architecture enables distributed processing across a network of child ECUs, creating a flexible, scalable control architecture that adapts to project requirements.

</div>

</details>

<details>
<summary><strong>Key Features</strong></summary>

<div style="margin-left: 20px;">

- Multi-platform support: ESP32-S3 (native) &  STM32/Arduino (via personality adapters)
- 8× CAT5 aux ports for child ECUs (Raspberry Pi, Jetson, ESP32, STM32, Arduino)
- Isolated CAN-FD transceiver for high-current device control
- 100 Mbps Ethernet connectivity
- 12V/24V input with 5V power distribution (≥5A total capacity)
- Designed for potting and long-term installations

</div>

</details>

<details>
<summary><strong>High-Level Component Diagram</strong></summary>

<div style="margin-left: 20px;">

```
          ┌────────────────────────────────────────┐
          |                                        │
    ┌─────▲───────┐    ┌───────┐ +5V               │
    │ Barrel Jack │───→│LM2576 │────┐       ┌──────▼───────┐
    │  12V/24V    │    │ Buck  │    │       │ 12/24V Fan   │
    └─────────────┘    └───────┘    │       └───────┬──────┘
                           │+5V     │               ▼
                           │        │  ┌────────────────────────┐
                           │        └─→│         ESP32-S3       │
                           │           │      (Motherboard)     │
                           │           └──▲──────────────▲──────┘
                           │              │              │
                           │         ┌────▼────┐    ┌────▼────┐
                           │         │LAN8720A │    │ADM3057E │
                           │         │Ethernet │    │ CAN-FD  │
                           │         └────▲────┘    └────▲────┘
                           │              │              │
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
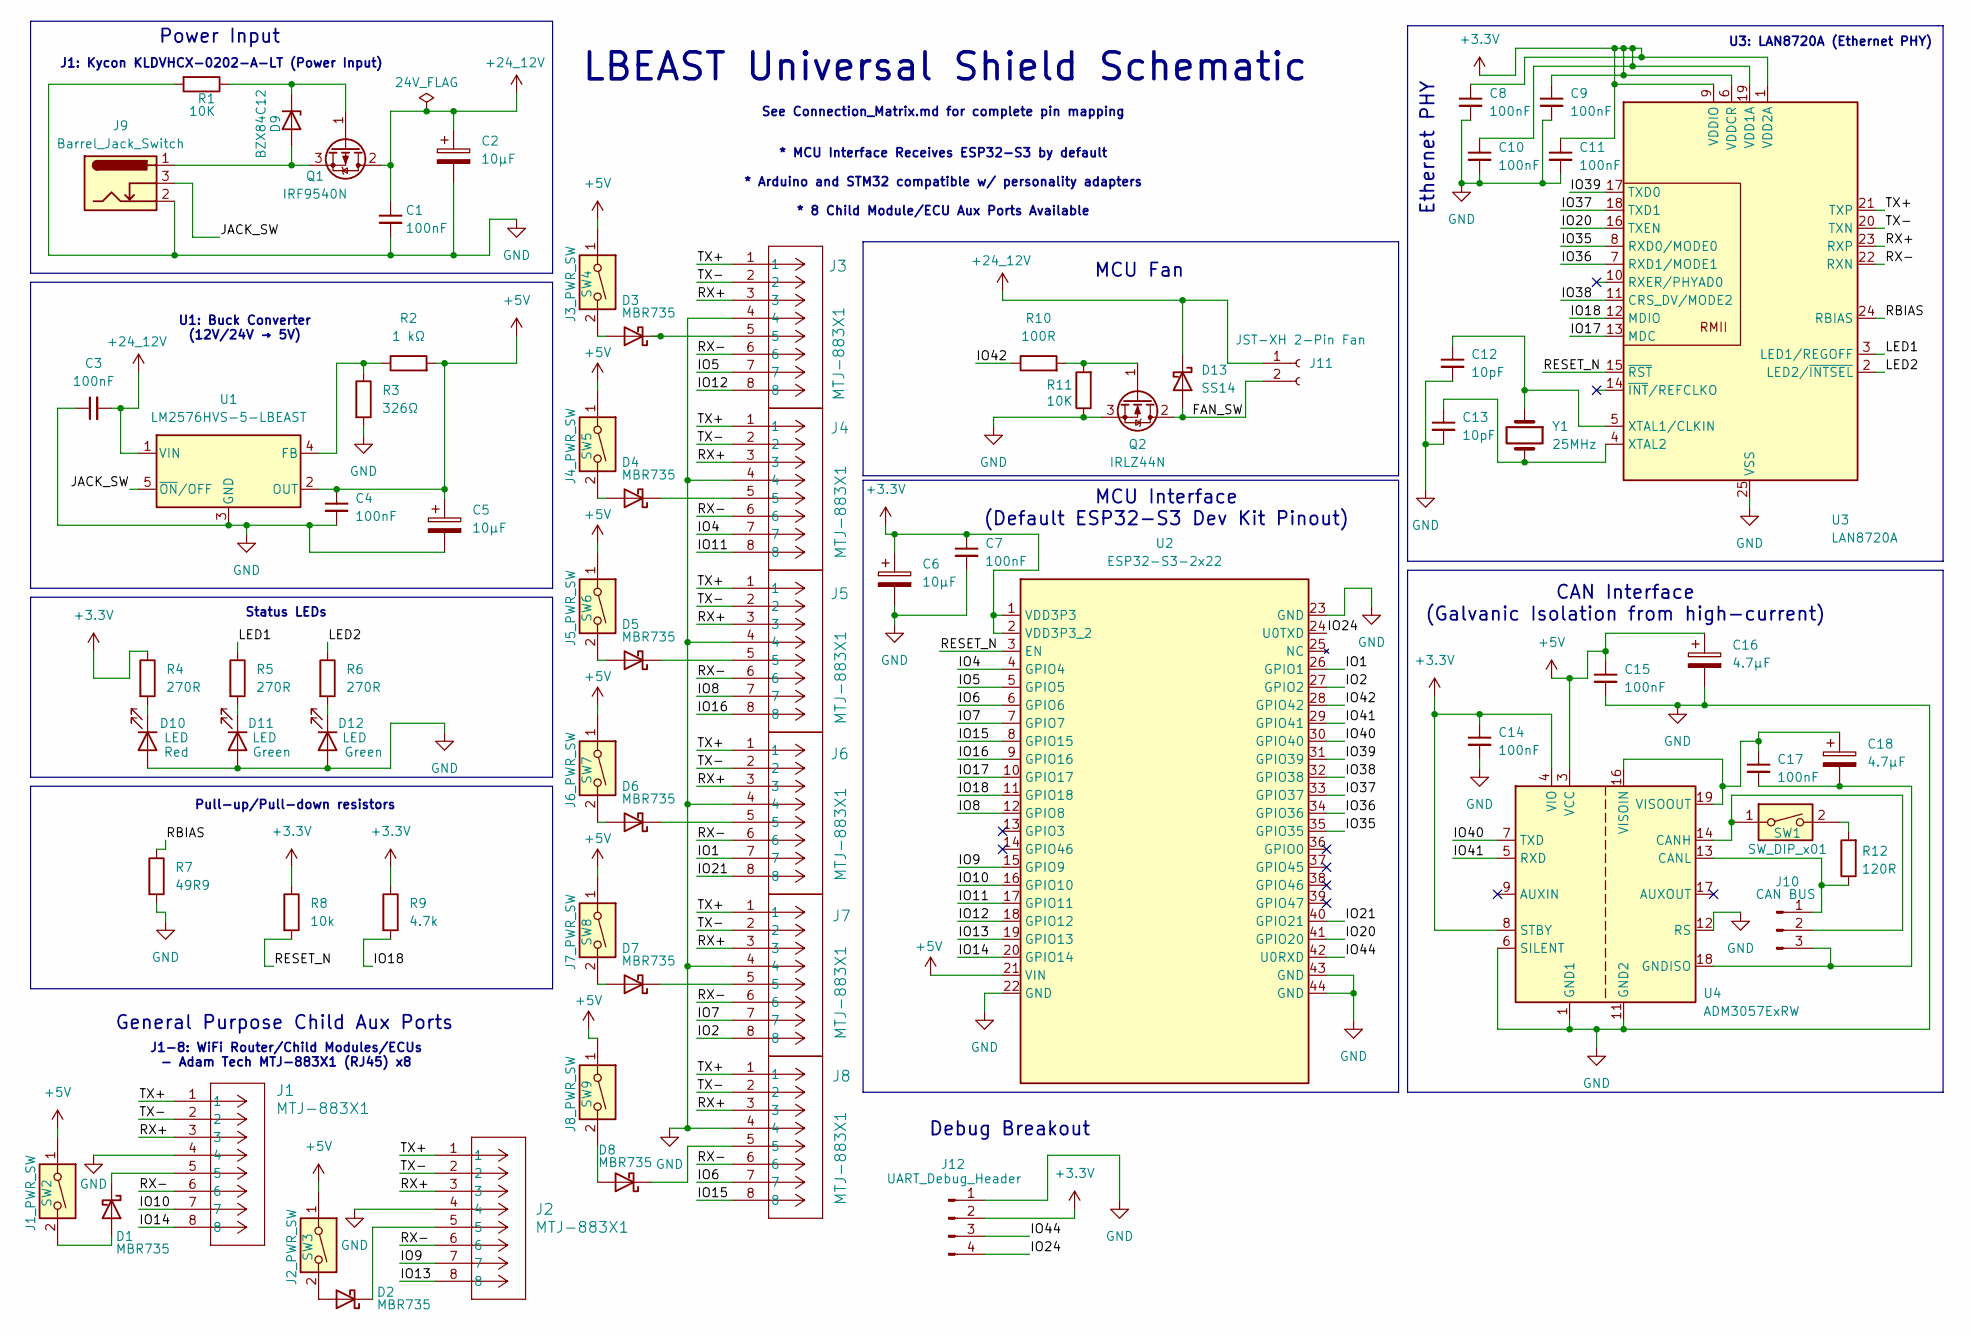
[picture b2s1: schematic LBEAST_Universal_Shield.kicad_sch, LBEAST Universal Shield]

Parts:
C1, C3, C4, C7, C8, C9, C10, C11, C14, C15, C17: 100nF; C_0805_2012Metric
C2: 10µF; CP_Radial_D6.3mm_P2.50mm
C5, C6: 10µF; CP_EIA-3216-18_Kemet-A
C12, C13: 10pF; C_0805_2012Metric
C16, C18: 4.7µF; CP_EIA-3216-18_Kemet-A
D1, D2, D3, D4, D5, D6, D7, D8: MBR735; TO-220-2_Vertical
D9: BZX84C12; SOT-23
D10, D11, D12: LED; LED_0805_2012Metric
D13: SS14; D_SMA
J1, J2, J3, J4, J5, J6, J7, J8: MTJ-883X1; CONN_MTJ-883X1_ADM
J9: Barrel_Jack_Switch; BarrelJack_Kycon_KLDX-0202-xC_Horizontal
J10: CAN BUS; JST_XH_B3B-XH-A_1x03_P2.50mm_Vertical
J11: JST-XH 2-Pin Fan; JST_XH_B2B-XH-AM_1x02_P2.50mm_Vertical
J12: UART_Debug_Header; PinHeader_1x04_P2.54mm_Vertical
Q1: IRF9540N; TO-220-3_Vertical
Q2: IRLZ44N; TO-220-3_Vertical
R1, R11: 10K; R_0805_2012Metric
R2: 1 kΩ; R_0805_2012Metric
R3: 326Ω; R_0805_2012Metric
R4, R5, R6: 270R; R_0805_2012Metric
R7: 49R9; R_0805_2012Metric
R8: 10k; R_0805_2012Metric
R9: 4.7k; R_0805_2012Metric
R10: 100R; R_0805_2012Metric
R12: 120R; R_0805_2012Metric
SW1: SW_DIP_x01; SW_DIP_SPSTx01_Slide_6.7x4.1mm_W6.73mm_P2.54mm_LowProfile_J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
SW2: J1_PWR_SW; SW_DIP_SPSTx01_Slide_6.7x4.1mm_W6.73mm_P2.54mm_LowProfile_J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
SW3: J2_PWR_SW; SW_DIP_SPSTx01_Slide_6.7x4.1mm_W6.73mm_P2.54mm_LowProfile_J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
SW4: J3_PWR_SW; SW_DIP_SPSTx01_Slide_6.7x4.1mm_W6.73mm_P2.54mm_LowProfile_J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
SW5: J4_PWR_SW; SW_DIP_SPSTx01_Slide_6.7x4.1mm_W6.73mm_P2.54mm_LowProfile_J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
SW6: J5_PWR_SW; SW_DIP_SPSTx01_Slide_6.7x4.1mm_W6.73mm_P2.54mm_LowProfile_J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
SW7: J6_PWR_SW; SW_DIP_SPSTx01_Slide_6.7x4.1mm_W6.73mm_P2.54mm_LowProfile_J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
SW8: J7_PWR_SW; SW_DIP_SPSTx01_Slide_6.7x4.1mm_W6.73mm_P2.54mm_LowProfile_J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
SW9: J8_PWR_SW; SW_DIP_SPSTx01_Slide_6.7x4.1mm_W6.73mm_P2.54mm_LowProfile_J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
U1: LM2576HVS-5-LBEAST; TO-263-5_TabPin3
U2: ESP32-S3-2x22; ESP32-S3_2x22_Header_v3
U3: LAN8720A; VQFN-24-1EP_4x4mm_P0.5mm_EP2.5x2.5mm_ThermalVias
U4: ADM3057ExRW; SOIC-20W_7.5x12.8mm_P1.27mm
Y1: 25MHz; Crystal_SMD_3225-4Pin_3.2x2.5mm

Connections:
+3.3V: C6.1, C7.1, C8.1, C9.1, C10.1, C11.1, C14.1, J12.2, R4.1, R8.1, R9.1, U2.1 (VDD3P3), U2.2 (VDD3P3_2), U3.1 (VDD2A), U3.6 (VDDCR), U3.9 (VDDIO), U3.19 (VDD1A), U4.4 (VIO), U4.8 (STBY)
+5V: C4.1, C5.1, C15.1, C16.1, R2.2, SW2.1, SW3.1, SW4.1, SW5.1, SW6.1, SW7.1, SW8.1, SW9.1, U1.2 (OUT), U2.21 (VIN), U4.3 (VCC)
+24_12V: C1.1, C2.1, C3.2, D13.1 (K), J11.1, Q1.2 (D), U1.1 (VIN)
/FAN_SW: D13.2 (A), J11.2, Q2.2 (D)
/IO1: J6.7, U2.26 (GPIO1)
/IO2: J7.8, U2.27 (GPIO2)
/IO4: J4.7, U2.4 (GPIO4)
/IO5: J3.7, U2.5 (GPIO5)
/IO6: J8.7, U2.6 (GPIO6)
/IO7: J7.7, U2.7 (GPIO7)
/IO8: J5.7, U2.12 (GPIO8)
/IO9: J2.7, U2.15 (GPIO9)
/IO10: J1.7, U2.16 (GPIO10)
/IO11: J4.8, U2.17 (GPIO11)
/IO12: J3.8, U2.18 (GPIO12)
/IO13: J2.8, U2.19 (GPIO13)
/IO14: J1.8, U2.20 (GPIO14)
/IO15: J8.8, U2.8 (GPIO15)
/IO16: J5.8, U2.9 (GPIO16)
/IO17: U2.10 (GPIO17), U3.13 (MDC)
/IO18: R9.2, U2.11 (GPIO18), U3.12 (MDIO)
/IO20: U2.41 (GPIO20), U3.16 (TXEN)
/IO21: J6.8, U2.40 (GPIO21)
/IO24: J12.4, U2.24 (U0TXD)
/IO35: U2.35 (GPIO35), U3.8 (RXD0/MODE0)
/IO36: U2.34 (GPIO36), U3.7 (RXD1/MODE1)
/IO37: U2.33 (GPIO37), U3.18 (TXD1)
/IO38: U2.32 (GPIO38), U3.11 (CRS_DV/MODE2)
/IO39: U2.31 (GPIO39), U3.17 (TXD0)
/IO40: U2.30 (GPIO40), U4.7 (TXD)
/IO41: U2.29 (GPIO41), U4.5 (RXD)
/IO42: R10.1, U2.28 (GPIO42)
/IO44: J12.3, U2.42 (U0RXD)
/JACK_SW: J9.3, U1.5 (~ON/OFF)
/LED1: R5.1, U3.3 (LED1/REGOFF)
/LED2: R6.1, U3.2 (LED2/~INTSEL)
/RBIAS: R7.1, U3.24 (RBIAS)
/RESET_N: R8.2, U2.3 (EN), U3.15 (~RST)
/RX+: J1.3, J2.3, J3.3, J4.3, J5.3, J6.3, J7.3, J8.3, U3.23 (RXP)
/RX-: J1.6, J2.6, J3.6, J4.6, J5.6, J6.6, J7.6, J8.6, U3.22 (RXN)
/TX+: J1.1, J2.1, J3.1, J4.1, J5.1, J6.1, J7.1, J8.1, U3.21 (TXP)
/TX-: J1.2, J2.2, J3.2, J4.2, J5.2, J6.2, J7.2, J8.2, U3.20 (TXN)
GND: C1.2, C2.2, C3.1, C4.2, C5.2, C6.2, C7.2, C8.2, C9.2, C10.2, C11.2, C12.2, C13.2, C14.2, C15.2, C16.2, D10.2 (A), D11.2 (A), D12.2 (A), J1.4, J2.4, J3.4, J4.4, J5.4, J6.4, J7.4, J8.4, J9.2, J12.1, Q2.3 (S), R1.2, R3.2, R7.2, R11.1, U1.3 (GND), U2.22 (GND), U2.23 (GND), U2.43 (GND), U2.44 (GND), U3.25 (VSS), U4.1 (GND1), U4.2 (GND1), U4.6 (SILENT), U4.10 (GND1), U4.11 (GND2), U4.12 (RS), U4.15 (GND2), Y1.3
unnamed: D1.2 (A), SW2.2
unnamed: D1.1 (K), J1.5
unnamed: D2.2 (A), SW3.2
unnamed: D2.1 (K), J2.5
unnamed: D3.2 (A), SW4.2
unnamed: D3.1 (K), J3.5
unnamed: D4.2 (A), SW5.2
unnamed: D4.1 (K), J4.5
unnamed: D5.2 (A), SW6.2
unnamed: D5.1 (K), J5.5
unnamed: D6.2 (A), SW7.2
unnamed: D6.1 (K), J6.5
unnamed: D7.2 (A), SW8.2
unnamed: D7.1 (K), J7.5
unnamed: D8.2 (A), SW9.2
unnamed: D8.1 (K), J8.5
unnamed: D9.1 (A), J9.1, Q1.3 (S)
unnamed: D9.3 (K), Q1.1 (G), R1.1
unnamed: D10.1 (K), R4.2
unnamed: D11.1 (K), R5.2
unnamed: D12.1 (K), R6.2
unnamed: J10.1, R12.1, U4.13 (CANL)
unnamed: J10.2, SW1.1, U4.14 (CANH)
unnamed: C17.2, C18.2, J10.3, U4.18 (GNDISO), U4.20 (GNDISO)
unnamed: Q2.1 (G), R10.2, R11.2
unnamed: R12.2, SW1.2
unnamed: R2.1, R3.1, U1.4 (FB)
unnamed: C12.1, U3.5 (XTAL1/CLKIN), Y1.1
unnamed: C13.1, U3.4 (XTAL2), Y1.2
unnamed: C17.1, C18.1, U4.16 (VISOIN), U4.19 (VISOOUT)

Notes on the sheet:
U1: Buck Converter (12V/24V → 5V)
J1-8: WiFi Router/Child Modules/ECUs - Adam Tech MTJ-883X1 (RJ45) x8
General Purpose Child Aux Ports
Debug Breakout
CAN Interface (Galvanic Isolation from high-current)
Ethernet PHY
Pull-up/Pull-down resistors
J1: Kycon KLDVHCX-0202-A-LT (Power Input)
MCU Fan
U3: LAN8720A (Ethernet PHY)
* MCU Interface Receives ESP32-S3 by default * Arduino and STM32 compatible w/ personality adapters * 8 Child Module/ECU Aux Ports Available
Power Input
See Connection_Matrix.md for complete pin mapping
LBEAST Universal Shield Schematic
Status LEDs
MCU Interface (Default ESP32-S3 Dev Kit Pinout)

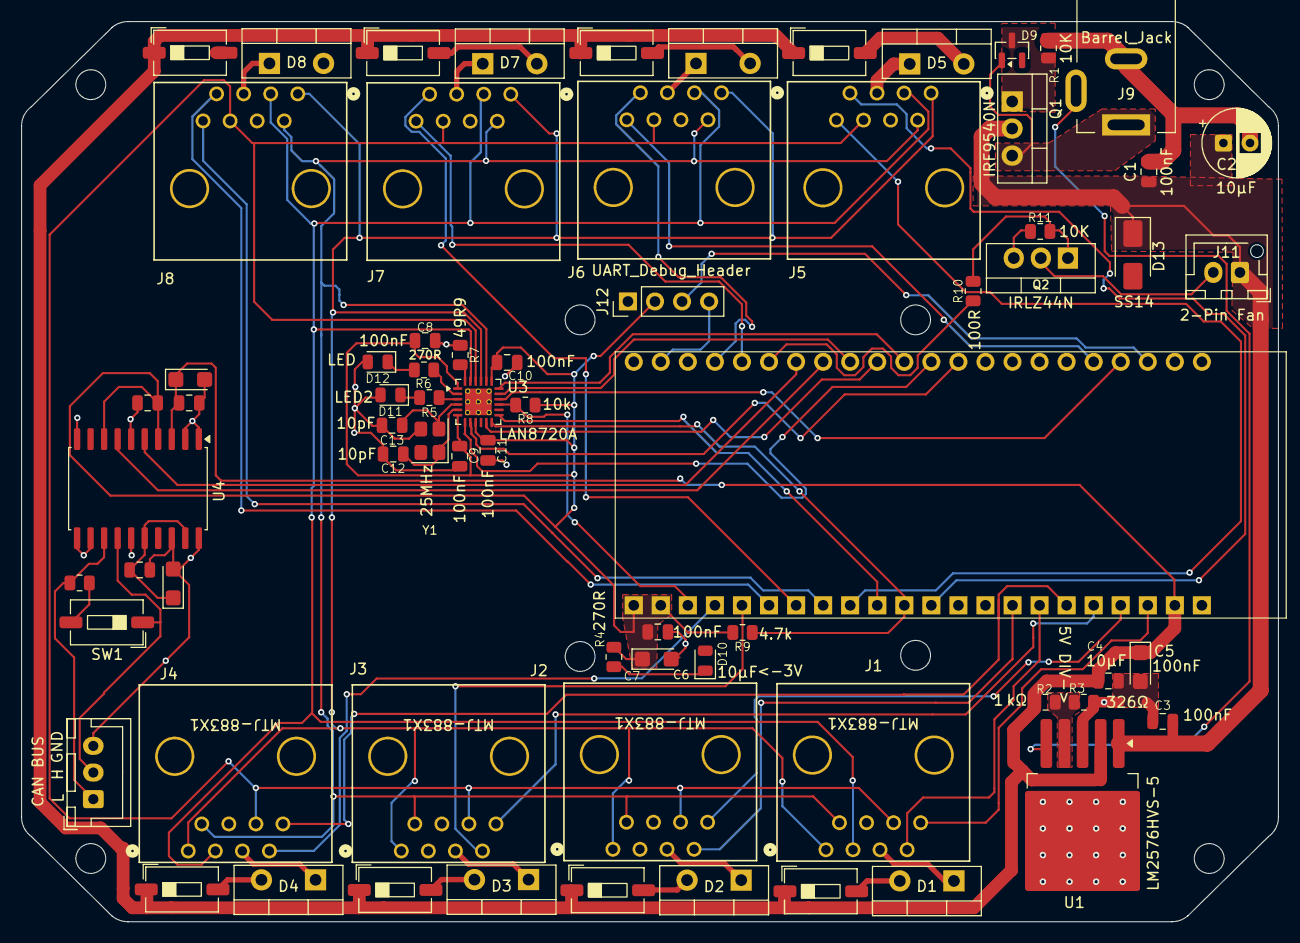
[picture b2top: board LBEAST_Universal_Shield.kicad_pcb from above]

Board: 2 copper layers, 118.0 x 84.5 mm, 71 parts (0 on the bottom side), 73 nets.

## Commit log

2025-10-26 flesh out EmbeddedSystems low-level transport, auth, encryption, and example sketch to connect to ESP32
2025-10-26 change actor refs to LiveActor
2025-10-26 clarify AActor vs Live Actor in docs
2025-10-26 add state machine control to AIFacemask template
2025-10-26 add author disclaimer
2025-10-26 adjust disclaimer formatting
2025-10-26 quick clarity update to readme
2025-10-27 add ServerManager to stand up Dedicated Server for AIFacemask template
2025-10-27 add Input Adapter for consolidating all input options
2025-10-31 add separate builds for dedicated servers versus command consoles
2025-10-31 consolidate docs
2025-11-01 add pro audio control to Command Console to sync digital mixer UI with physical front-of-house sound boards from Behringer, Yamaha, etc.
2025-11-02 restructure repo to be plugin-install-friendly
2025-11-02 resolve circular dependencies
2025-11-05 add pro lighting system
2025-11-08 add escape room experience and door lock example firmware
2025-11-08 add scissor lift controller & actuator controller to firmware examples and use both in new GunshipExperience ECU
2025-11-09 resolve compiler errors'
2025-11-09 add VOIP with Mumble and Steam Audio 3D HRTFs
2025-11-09 add logo and update docs
2025-11-09 add crosslink to unity version
2025-11-09 add skeletal structure of AIFacemask implementation
2025-11-10 add standard layout to readme
2025-11-10 big UDP refactor super-classing and subclassing transport to eliminate project-wide transport code duplication, and add model structs for MVC pattern in Experiences-to-EmbeddedSystems transport funct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
2025-11-10 add FlightSimExperience and Flight sim ECU
2025-11-12 add Gun ECU to Gunship experience
2025-11-12 clean up readme
2025-11-13 add retail payment interface for tap-card or tap-wristband
2025-11-13 cleanup Gun ECU errors
2025-11-13 add world position manual/auto calibration (AKA PCFs for SteamVR)
2025-11-13 add skaffolding for the go kart experience
2025-11-14 add 433MHz interface
2025-11-14 add Superhero Flight Experience
2025-11-14 update README author disclaimer and version badge
2025-11-14 update roadmap
2025-11-14 add multiplayer head/hands transport
2025-11-15 finish 1.0 LBEASTAI API and AIFacemask implementation
2025-11-15 add AGENTS.md to make LBEAST agent-friendly
2025-11-19 1st draft of universal shield schematic
2025-11-20 refresh README
2025-11-21 add alpha universal shield schematic
2025-11-24 complete alpha Universal Shield PCB
2025-11-24 update documentation to conform to new uni-shield pcb alpha release
2025-11-25 add power differential protection to LBUS aux ports
2025-11-26 integrate new ECUs into firmware code mapping
2025-11-26 update README formatting
2025-11-29 update LBUS
2025-11-30 add labels to pcb image in readme
2025-12-04 add links to OnShape codebase
2025-12-05 add author framing recommendations

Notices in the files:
README.md:
📄 License:
Copyright (c) 2025 AJ Campbell
Licensed under the MIT License. See [LICENSE](LICENSE) for details.
License: MIT
LBEAST is open-source under the MIT License. Got ideas for how to make LBEAST better? Contributions are welcome!
